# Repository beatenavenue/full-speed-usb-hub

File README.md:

**ATTENTION: THIS PRODUCT NOT YET WORKING**

# SLOWER SPEED USB HUB
4 port USB2.0 HUB limit by full speed (slow like 1.1)

## Motivation
My DIY USB hardware is susceptible to noise and cannot reliably carry high-bit-rate signals over inexpensive jumper wires.  
To work around this, I used a legacy USB 1.1 low-bit-rate device: by inserting a USB 1.1 hub I could force the link to downgrade, which solved the problem completely.  
Unfortunately, USB 1.1 devices are now out of stock, so I can no longer apply the same workaround.

I have recently found a USB 2.0 isolator chip. Although USB 2.0 normally operates at 480 Mbps (Hi-Speed), this chip limits the data rate to 12 Mbps or 1.5 Mbps while still conforming to the USB 2.0 protocol. Because the lower data rate uses lower signalling frequencies, it should mitigate the noise issues just as USB 1.1 did.

## Solution
- **ADuM4160** — USB 2.0 isolator chip  
- **CH334P** — USB 2.0 hub-controller chip

## Dependency Library
- [TLV73330PDBVR](https://www.snapeda.com/parts/TLV73330PDBVR/Texas%20Instruments/view-part/?ref=search&t=TLV73330PDBVR)

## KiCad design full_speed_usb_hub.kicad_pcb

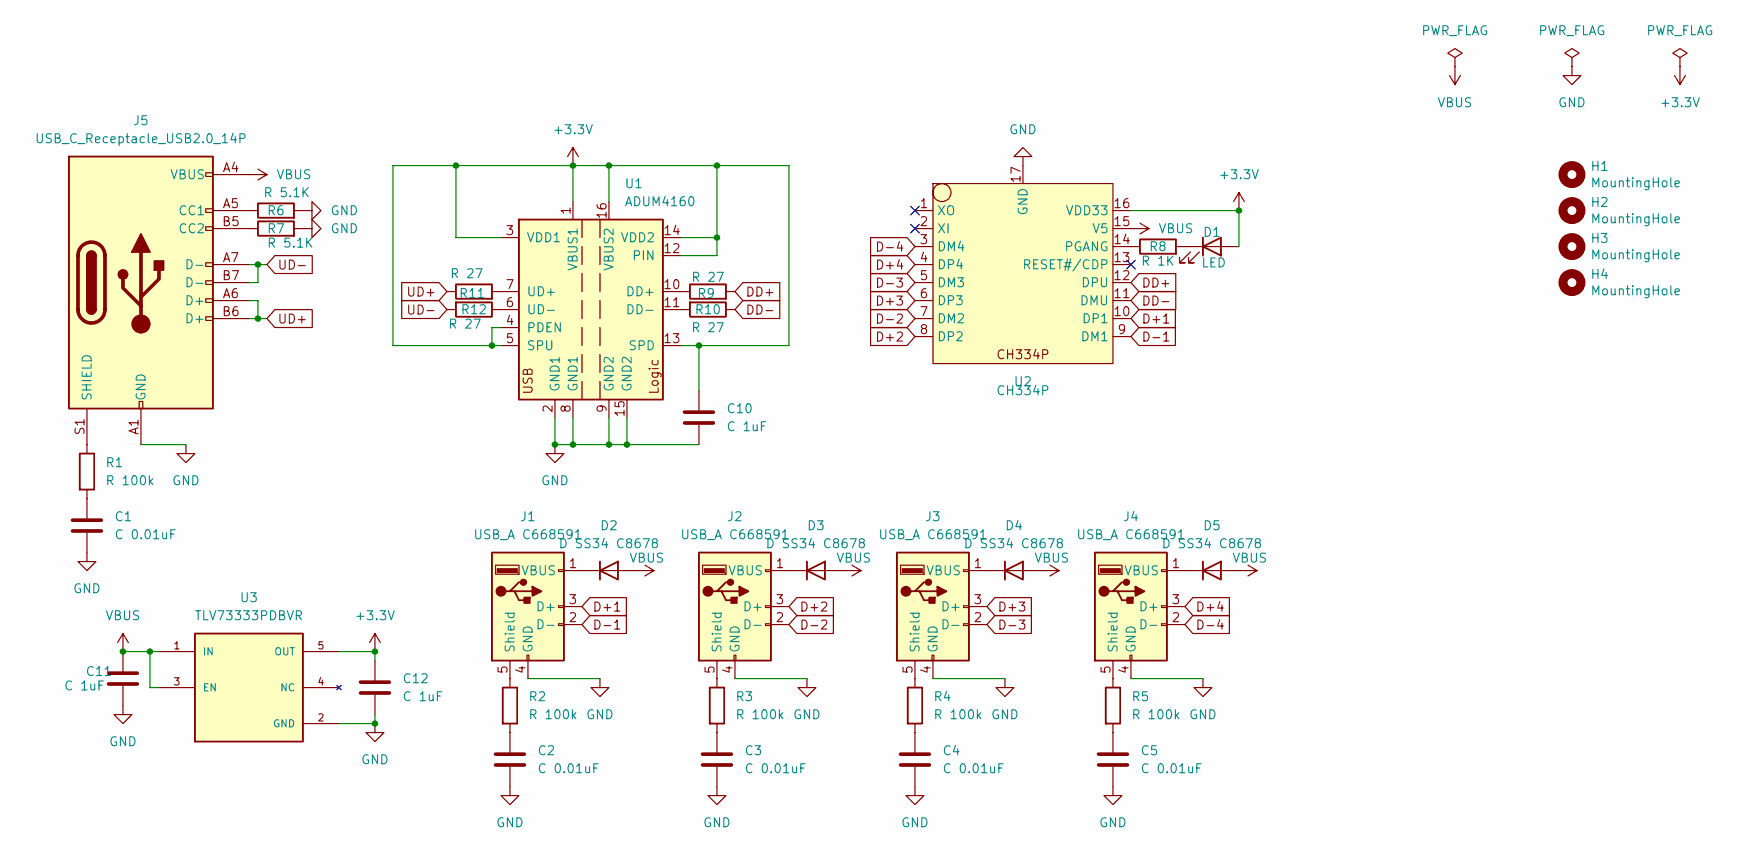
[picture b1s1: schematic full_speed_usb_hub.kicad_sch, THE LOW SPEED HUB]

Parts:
C1, C2, C3, C4, C5: C 0.01uF; C_1206_3216Metric
C10, C11, C12: C 1uF; C_1206_3216Metric
D1: LED; LED_0603_1608Metric
D2, D3, D4, D5: D SS34 C8678; D_SMA
H1, H2, H3, H4: MountingHole; MountingHole_2.2mm_M2
J1, J2, J3, J4: USB_A C668591; USB_A_Receptacle_C668591
J5: USB_C_Receptacle_USB2.0_14P; USB_C_Receptacle_HCTL_HC-TYPE-C-16P-01A
R1, R2, R3, R4, R5: R 100k; R_0603_1608Metric
R6, R7: R 5.1K; R_0603_1608Metric
R8: R 1K; R_0603_1608Metric
R9, R10, R11, R12: R 27; R_0603_1608Metric
U1: ADUM4160; SOIC-16W_7.5x10.3mm_P1.27mm
U2: CH334P
U3: TLV73333PDBVR; SOT95P280X145-5N; PARTREV C; DigiKey_Part_Number 296-40673-2-ND

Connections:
+3.3V: C10.1, C12.1, D1.2 (A), U1.1 (VBUS1), U1.3 (VDD1), U1.4 (PDEN), U1.5 (SPU), U1.12 (PIN), U1.13 (SPD), U1.14 (VDD2), U1.16 (VBUS2), U2.16 (VDD33), U3.5 (OUT)
D+1: J1.3 (D+), U2.10 (DP1)
D+2: J2.3 (D+), U2.8 (DP2)
D+3: J3.3 (D+), U2.6 (DP3)
D+4: J4.3 (D+), U2.4 (DP4)
D-1: J1.2 (D-), U2.9 (DM1)
D-2: J2.2 (D-), U2.7 (DM2)
D-3: J3.2 (D-), U2.5 (DM3)
D-4: J4.2 (D-), U2.3 (DM4)
DD+: R9.2, U2.12 (DPU)
DD-: R10.1, U2.11 (DMU)
GND: C1.2, C2.2, C3.2, C4.2, C5.2, C10.2, C11.2, C12.2, J1.4 (GND), J2.4 (GND), J3.4 (GND), J4.4 (GND), J5.A1 (GND), J5.A12 (GND), J5.B1 (GND), J5.B12 (GND), R6.2, R7.2, U1.2 (GND1), U1.8 (GND1), U1.9 (GND2), U1.15 (GND2), U2.17 (GND), U3.2 (GND)
unnamed: C1.1, R1.2
unnamed: C2.1, R2.2
unnamed: C3.1, R3.2
unnamed: C4.1, R4.2
unnamed: C5.1, R5.2
unnamed: D1.1 (K), R8.2
unnamed: D2.1 (K), J1.1 (VBUS)
unnamed: D3.1 (K), J2.1 (VBUS)
unnamed: D4.1 (K), J3.1 (VBUS)
unnamed: D5.1 (K), J4.1 (VBUS)
unnamed: J1.5 (Shield), R2.1
unnamed: J2.5 (Shield), R3.1
unnamed: J3.5 (Shield), R4.1
unnamed: J4.5 (Shield), R5.1
unnamed: J5.A5 (CC1), R6.1
unnamed: J5.B5 (CC2), R7.1
unnamed: J5.S1 (SHIELD), R1.1
unnamed: R9.1, U1.10 (DD+)
unnamed: R10.2, U1.11 (DD-)
unnamed: R11.2, U1.7 (UD+)
unnamed: R12.1, U1.6 (UD-)
unnamed: R8.1, U2.14 (PGANG)
UD+: J5.A6 (D+), J5.B6 (D+), R11.1
UD-: J5.A7 (D-), J5.B7 (D-), R12.2
VBUS: C11.1, D2.2 (A), D3.2 (A), D4.2 (A), D5.2 (A), J5.A4 (VBUS), J5.A9 (VBUS), J5.B4 (VBUS), J5.B9 (VBUS), U2.15 (V5), U3.1 (IN), U3.3 (EN)

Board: 2 copper layers, 37 parts (0 on the bottom side), 37 nets, no tracks yet.

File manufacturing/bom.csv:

Designator,Footprint,Quantity,Value,LCSC Part #
"C1, C2, C3, C4, C5",1206,5,C 0.01uF,"C1846"
"C10, C11, C12",1206,3,C 1uF,"C1848"
D1,0603,1,LED,"C2286"
"D2, D3, D4, D5",D_SMA,4,D SS34 C8678,"C8678"
"J1, J2, J3, J4",USB_A_Receptacle_C668591,4,USB_A C668591,"C668591"
J5,USB_C_Receptacle_HCTL_HC-TYPE-C-16P-01A,1,USB_C_Receptacle_USB2.0_14P,"C165948"
"R1, R2, R3, R4, R5",0603,5,R 100k,"C25803"
"R10, R11, R12, R9",0603,4,R 27,"C2907018"
"R6, R7",0603,2,R 5.1K,"C23186"
R8,0603,1,R 1K,"C21190"
U1,SOIC-16W_7.5x10.3mm_P1.27mm,1,ADUM4160,"C579406"
U2,CH334P,1,CH334P,"C5373042"
U3,SOT95P280X145-5N,1,TLV73333PDBVR,"C134139"

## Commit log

2025-07-22 KiCAD Design
2025-07-22 manufacturing (for JLCPCB)
2025-08-03 update BOM and order PCBA
2025-08-08 add pcba image
